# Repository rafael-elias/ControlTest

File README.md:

# ControlTest
Trabalho de Conclusão de Curso de Engenharia de Controle e Automação:
[Ifes - Campus Serra](https://serra.ifes.edu.br)

## Plataforma Didática para Implementação e Avaliação de Controladores Discretos

 - Plataforma composta por hardware (Arduino Nano + Componentes Complementares) e software supervisório.
 - Tem por objetivo proporcionar o teste e avaliação de projetos de controladores discretos em plantas reais.

## Supervisório

Tela Principal:

Tela de configuração dos controladores:

## Arduino

- Programa "Proj_SisCont" implementado no Arduino gerencia o hardware da plataforma.
- Utilizado Arduino Nano V3.0. 

## Placa

- Esquema e PCB do hardware da plataforma (Arduino + Componentes Complementares). 

## Releases
- Primeira versão para instalação do supervisório: [ControlTest_Sup_1.0.0_Win32.7z](https://github.com/rafael-elias/ControlTest/releases/tag/v1.0.0)

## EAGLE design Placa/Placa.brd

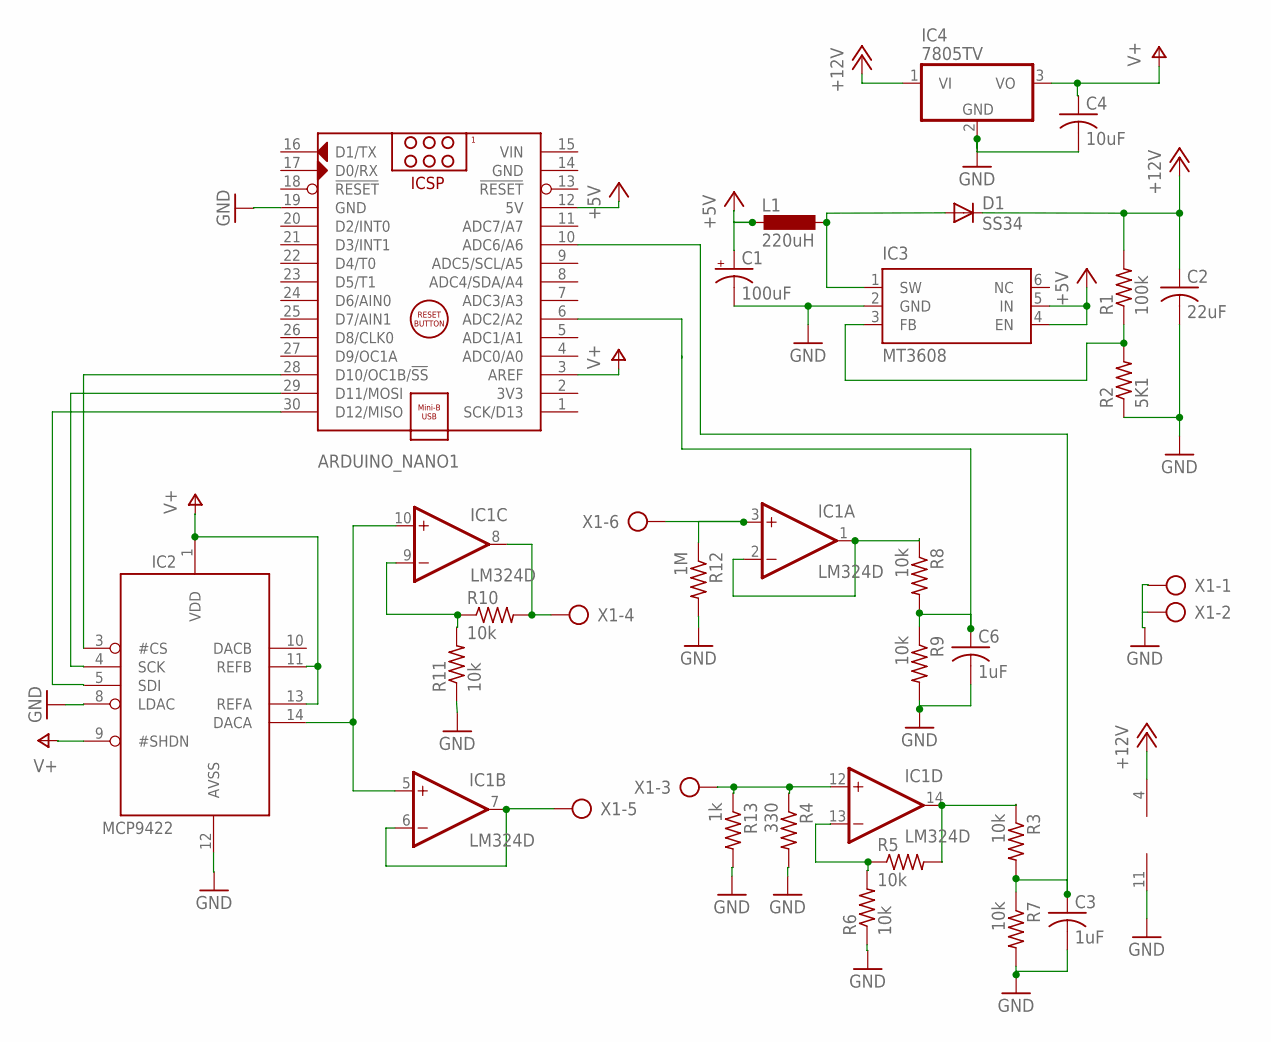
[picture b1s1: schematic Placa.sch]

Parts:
ARDUINO_NANO1: ARDUINO_NANO
C1: 100uF; E2,5-6
C2: 22uF; C1206
C3, C6: 1uF; C0805
C4: 10uF; C0805
D1: SS34; DO-214AC
IC1: LM324D; SO14
IC2: MCP4922; SO14
IC3: MT3608; SOT23-6
IC4: 7805TV; TO220V
L1: 220uH; DO3316P
R1: 100k; R0805
R2: 5K1; R0805
R3, R5, R6, R7, R8, R9, R10, R11: 10k; R0805
R4: 330; R0805
R12: 1M; R0805
R13: 1k; R0805
X1: AK500/6

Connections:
+5V: ARDUINO_NANO1.12 (5V), C1.+, IC3.4 (EN), IC3.5 (IN), L1.1
+12V: C2.1, D1.C, IC1.4 (V+), IC4.1 (VI), R1.2
GND: ARDUINO_NANO1.14 (GND), ARDUINO_NANO1.19 (GND), C1.-, C2.2, C3.2, C4.2, C6.2, IC1.11 (V-), IC2.8 (LDAC), IC2.12 (AVSS), IC3.2 (GND), IC4.2 (GND), R2.1, R4.2, R6.1, R7.2, R9.2, R11.1, R12.2, R13.2, X1.1, X1.2
unnamed: D1.A, IC3.1 (SW), L1.2
unnamed: ARDUINO_NANO1.28 (D10/OC1B/!SS), IC2.3 (#CS)
unnamed: ARDUINO_NANO1.29 (D11/MOSI), IC2.4 (SCK)
unnamed: ARDUINO_NANO1.30 (D12/MISO), IC2.5 (SDI)
unnamed: IC3.3 (FB), R1.1, R2.2
unnamed: IC1.14 (OUT), R3.1, R5.2
unnamed: IC1.9 (-IN), R10.1, R11.2
unnamed: IC1.12 (+IN), R4.1, R13.1, X1.3
unnamed: IC1.13 (-IN), R5.1, R6.2
unnamed: ARDUINO_NANO1.6 (ADC2/A2), C6.1, R8.2, R9.1
unnamed: IC1.3 (+IN), R12.1, X1.6
unnamed: IC1.1 (OUT), IC1.2 (-IN), R8.1
unnamed: IC1.6 (-IN), IC1.7 (OUT), X1.5
unnamed: IC1.8 (OUT), R10.2, X1.4
unnamed: IC1.5 (+IN), IC1.10 (+IN), IC2.14 (DACA)
unnamed: ARDUINO_NANO1.10 (ADC6/A6), C3.1, R3.2, R7.1
V+: ARDUINO_NANO1.3 (AREF), C4.1, IC2.1 (VDD), IC2.9 (#SHDN), IC2.11 (REFB), IC2.13 (REFA), IC4.3 (VO)
VIN: ARDUINO_NANO1.15 (VIN)

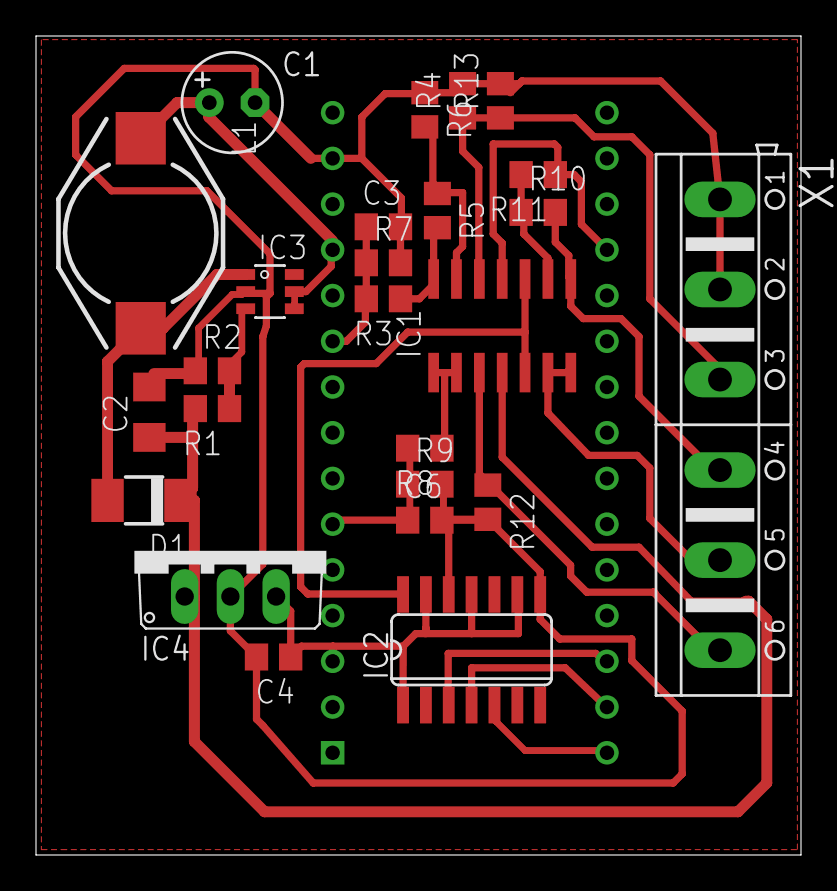
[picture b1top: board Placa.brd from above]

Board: 2 copper layers, 42.5 x 45.5 mm, 26 parts (1 on the bottom side), 20 nets.

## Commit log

2021-04-18 Telas
    Telas do supervisório
2021-04-18 Revert "Telas"
    This reverts commit 59b45c155766d37ee51ae4d9193f41dd423b1869.
2021-04-18 Adicionado print das telas
2021-04-18 Adicionado arquivos Eagle
    Arquivos Eagle contendo esquema e placa para a montagem do hardware da plataforma didática.
2022-08-03 Habilitado FB corrente
    Habilitado feedback em corrente.
